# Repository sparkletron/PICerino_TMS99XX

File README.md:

# PICerino TMS VDP

Test Board and Software Library for TI TMS992X and TMS9118 video display processors.

author: Jay Convertino  

date: 2022.04.23  

license: MIT (software/Hardware)

## Release Versions
### Current
  - v2.1.0 - Improved video circuit for the TMS9118.

### Past
  - v2.0.0 - Improved video circuit that actually works.
  - v1.0.0 - Improved video circuit and TMS9118 schematic added.
  - v0.5.0 - First version with old video circuit.
  - none
  
## Requirements
### Hardware
  - KiCad
  
### Software
  - xc8 compiler
  
## Information

### Directory Listing:

  - docs - Data documents for various ICs.
  - schematic - KiCad schematic
    - TMS9118 - Contains a schematic for a TMS9118 board with video circuit (v2).
    - TMS992X - Contains a schematic for a TMS992X board with video circuit (v2).
  - src - Any source code for the project.
    - lib_picTMS99XX folder contains a library with test program for picerino. See readme.md in this directory for details.

### Usage
  This is made to be used with the picerino development board. This uses the standard DRAM since there are plenty of them around from various venders. The idea is the test program with put the card through its paces. This is done by putting the VDP into all modes and testing all of its functions. Currently this is incomplete. GFX II, various sprite sizes and edge cases need testing. The other idea with this was to create a simple video circuit for YrYbY output to go to an upscaler and then to HDMI. The retrotink 2x works well with the output of this unit.

### Build
  Through hole components were selected for everything, except for the video circuit of the TMS9118. This something I had on hand. Production uses a double sided board.

### Video Output
  This video circuit is based on a few ideas. Mostly TMS-RGB for the use of the LM1881. All other design choices are from application datasheets and just trial and error. Main issue with TMS-RGB being used whole sale is it has all surface mount components and it isn't universal for TMS9918. The goal of this project was to output component or composite to the retro tink x2. TI's application data sheet is keying out the Yr/Yb color bursts with a decoulping cap passing the signal to a 4066 that just went to ground during sync. This in theory should work fine, but in practice you'll still see a bit of the burst. TMS-RGB used a sample and hold method, which worked great to the converter chip. Taking the TMS RGB and just using a quad switch to sample the Yb signal, then pass it to the other inputs that then use that sample when needed (see lm1881 connections). This method of using a quad switch eliminates the too much blue issue. It also results in a circuit that is only 3 ic's. A MAX394, ADG813, and LM1881. The opamp is setup to rebalance the colors per the TMS RGB Y+Yr+Yb findings. Again big thanks to them for spending the time to document how and what they did. Saved me a lot of work on this project.

### Issues
  N/A

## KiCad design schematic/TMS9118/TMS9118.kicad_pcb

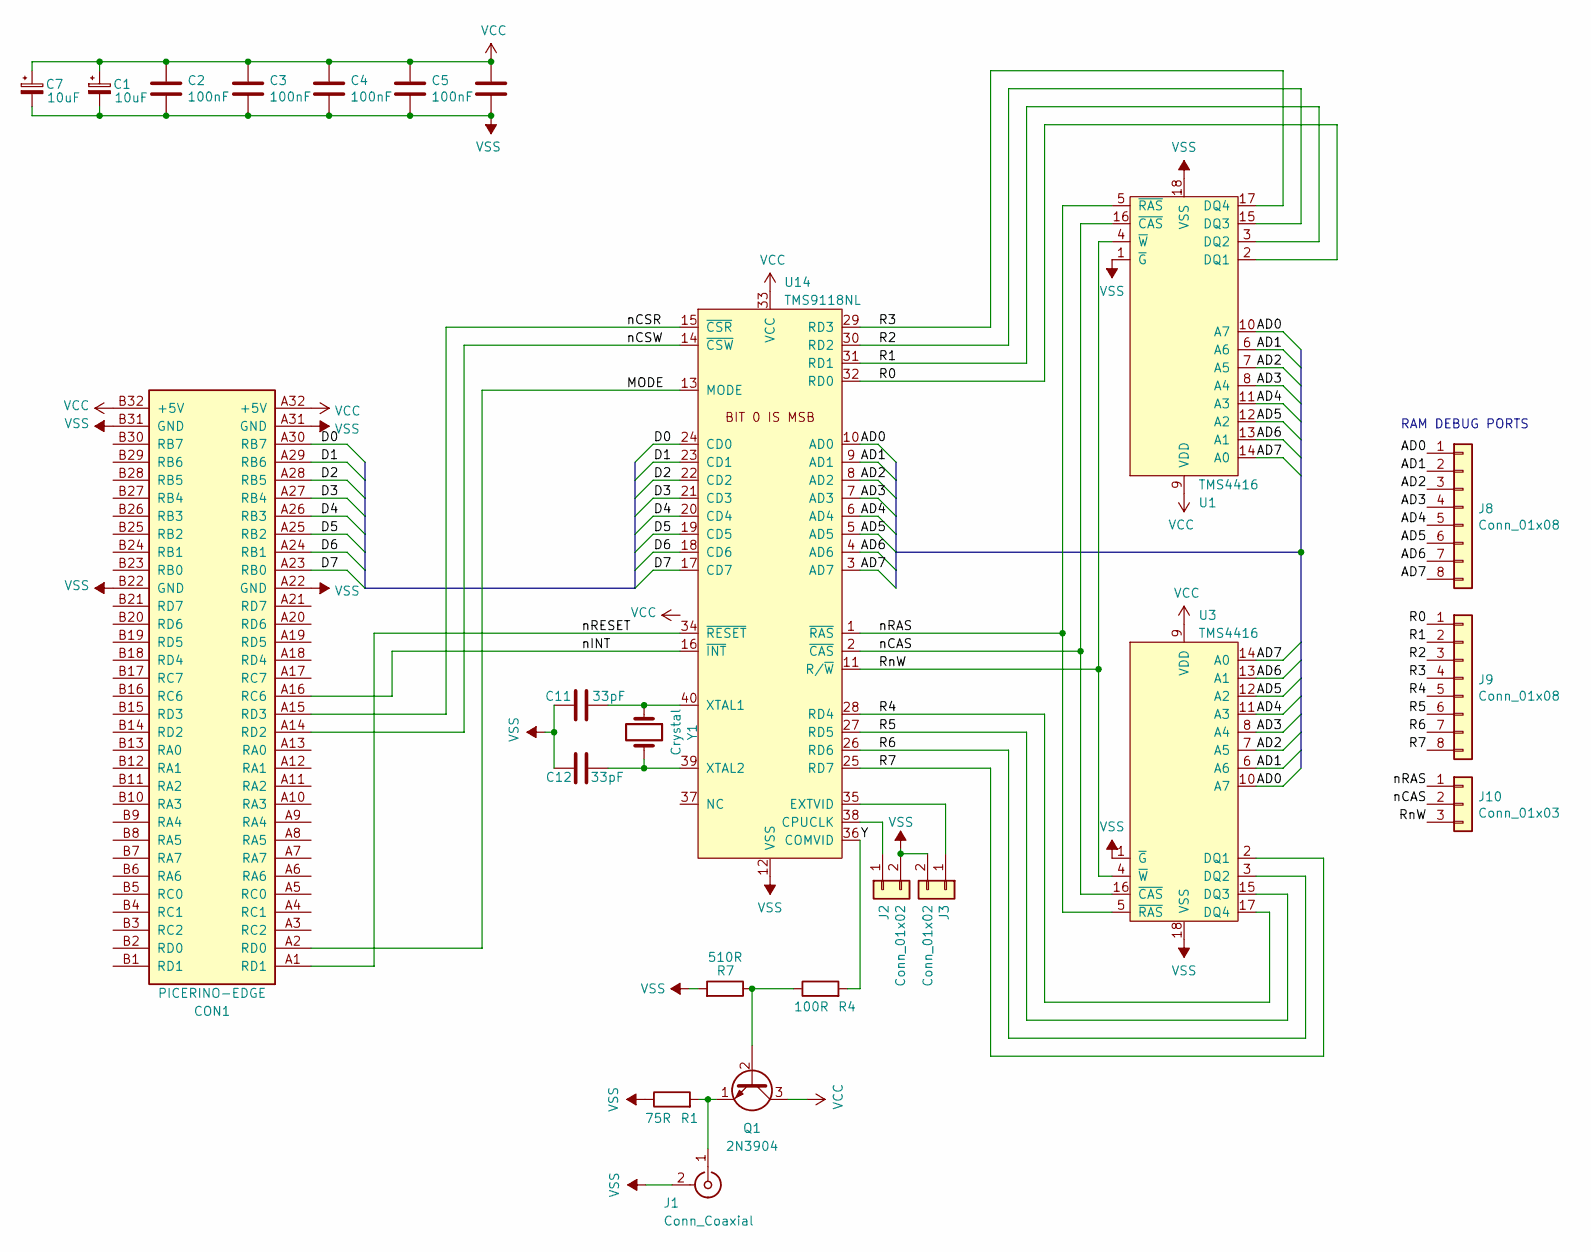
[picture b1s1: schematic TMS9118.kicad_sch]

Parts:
C1, C7: 10uF; CP_Radial_D5.0mm_P2.50mm
C2, C3, C4, C5, C6: 100nF; C_Disc_D4.7mm_W2.5mm_P5.00mm
C11, C12: 33pF; C_Disc_D3.0mm_W1.6mm_P2.50mm
CON1: PICERINO-EDGE
J1: Conn_Coaxial; RCJ041
J2, J3: Conn_01x02; PinHeader_1x02_P2.54mm_Vertical
J8, J9: Conn_01x08; SIP-8_19x3mm_P2.54mm
J10: Conn_01x03; PinHeader_1x03_P2.54mm_Vertical
Q1: 2N3904; TO-92_Wide
R1: 75R; R_Axial_DIN0207_L6.3mm_D2.5mm_P7.62mm_Horizontal
R4: 100R; R_Axial_DIN0207_L6.3mm_D2.5mm_P7.62mm_Horizontal
R7: 510R; R_Axial_DIN0207_L6.3mm_D2.5mm_P7.62mm_Horizontal
U1, U3: TMS4416; DIP-18_W7.62mm_LongPads
U14: TMS9118NL; DIP-40_W15.24mm_LongPads
Y1: Crystal; Crystal_HC49-4H_Vertical

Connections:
/AD0: J8.1, U1.10 (A7), U3.10 (A7), U14.10 (AD0)
/AD1: J8.2, U1.6 (A6), U3.6 (A6), U14.9 (AD1)
/AD2: J8.3, U1.7 (A5), U3.7 (A5), U14.8 (AD2)
/AD3: J8.4, U1.8 (A4), U3.8 (A4), U14.7 (AD3)
/AD4: J8.5, U1.11 (A3), U3.11 (A3), U14.6 (AD4)
/AD5: J8.6, U1.12 (A2), U3.12 (A2), U14.5 (AD5)
/AD6: J8.7, U1.13 (A1), U3.13 (A1), U14.4 (AD6)
/AD7: J8.8, U1.14 (A0), U3.14 (A0), U14.3 (AD7)
/D0: CON1.A30 (RB7), U14.24 (CD0)
/D1: CON1.A29 (RB6), U14.23 (CD1)
/D2: CON1.A28 (RB5), U14.22 (CD2)
/D3: CON1.A27 (RB4), U14.21 (CD3)
/D4: CON1.A26 (RB3), U14.20 (CD4)
/D5: CON1.A25 (RB2), U14.19 (CD5)
/D6: CON1.A24 (RB1), U14.18 (CD6)
/D7: CON1.A23 (RB0), U14.17 (CD7)
/MODE: CON1.A2 (RD0), U14.13 (MODE)
/R0: J9.1, U1.2 (DQ1), U14.32 (RD0)
/R1: J9.2, U1.3 (DQ2), U14.31 (RD1)
/R2: J9.3, U1.15 (DQ3), U14.30 (RD2)
/R3: J9.4, U1.17 (DQ4), U14.29 (RD3)
/R4: J9.5, U3.17 (DQ4), U14.28 (RD4)
/R5: J9.6, U3.15 (DQ3), U14.27 (RD5)
/R6: J9.7, U3.3 (DQ2), U14.26 (RD6)
/R7: J9.8, U3.2 (DQ1), U14.25 (RD7)
/RnW: J10.3, U1.4 (~W), U3.4 (~W), U14.11 (R/~W)
/Y: R4.2, U14.36 (COMVID)
/nCAS: J10.2, U1.16 (~CAS), U3.16 (~CAS), U14.2 (~CAS)
/nCSR: CON1.A15 (RD3), U14.15 (~CSR)
/nCSW: CON1.A14 (RD2), U14.14 (~CSW)
/nINT: CON1.A16 (RC6), U14.16 (~INT)
/nRAS: J10.1, U1.5 (~RAS), U3.5 (~RAS), U14.1 (~RAS)
/nRESET: CON1.A1 (RD1), U14.34 (~RESET)
unnamed: J1.1 (In), Q1.1 (E), R1.2
unnamed: J2.1, U14.38 (CPUCLK)
unnamed: J3.1, U14.35 (EXTVID)
unnamed: Q1.2 (B), R4.1, R7.1
unnamed: C11.2, U14.40 (XTAL1), Y1.1
unnamed: C12.1, U14.39 (XTAL2), Y1.2
VCC: C1.1, C2.1, C3.1, C4.1, C5.1, C6.1, C7.1, CON1.A32 (+5V), CON1.B32 (+5V), Q1.3 (C), U1.9 (VDD), U3.9 (VDD), U14.33 (VCC)
VSS: C1.2, C2.2, C3.2, C4.2, C5.2, C6.2, C7.2, C11.1, C12.2, CON1.A22 (GND), CON1.A31 (GND), CON1.B22 (GND), CON1.B31 (GND), J1.2 (Ext), J2.2, J3.2, R1.1, R7.2, U1.1 (~G), U1.18 (VSS), U3.1 (~G), U3.18 (VSS), U14.12 (VSS)

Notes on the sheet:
RAM DEBUG PORTS

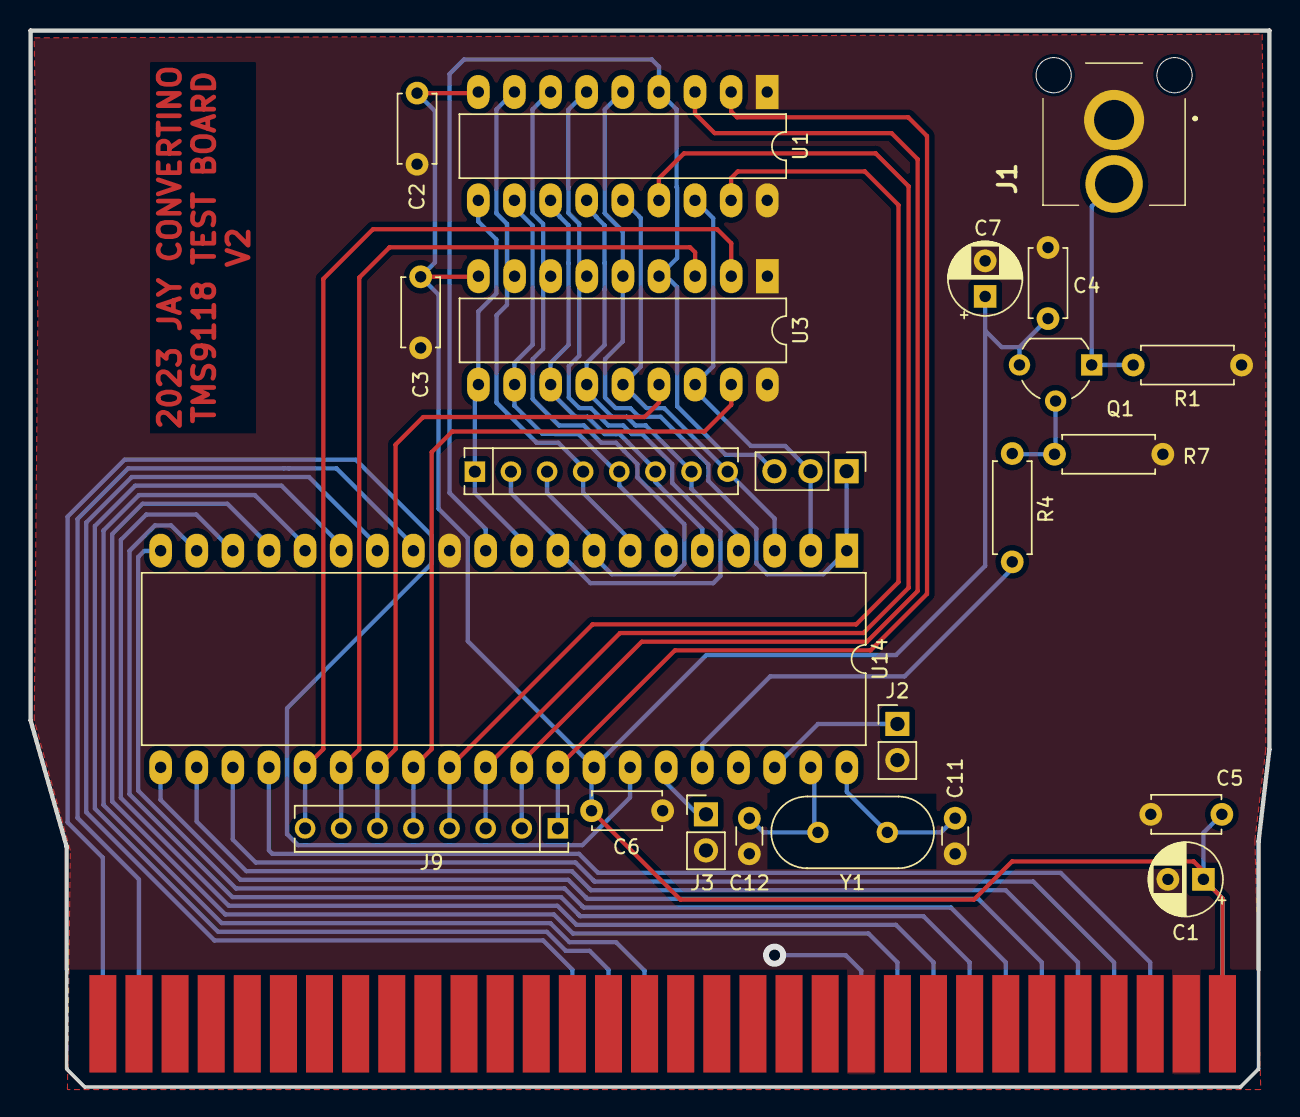
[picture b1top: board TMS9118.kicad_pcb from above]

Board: 2 copper layers, 87.1 x 74.3 mm, 24 parts (0 on the bottom side), 41 nets.

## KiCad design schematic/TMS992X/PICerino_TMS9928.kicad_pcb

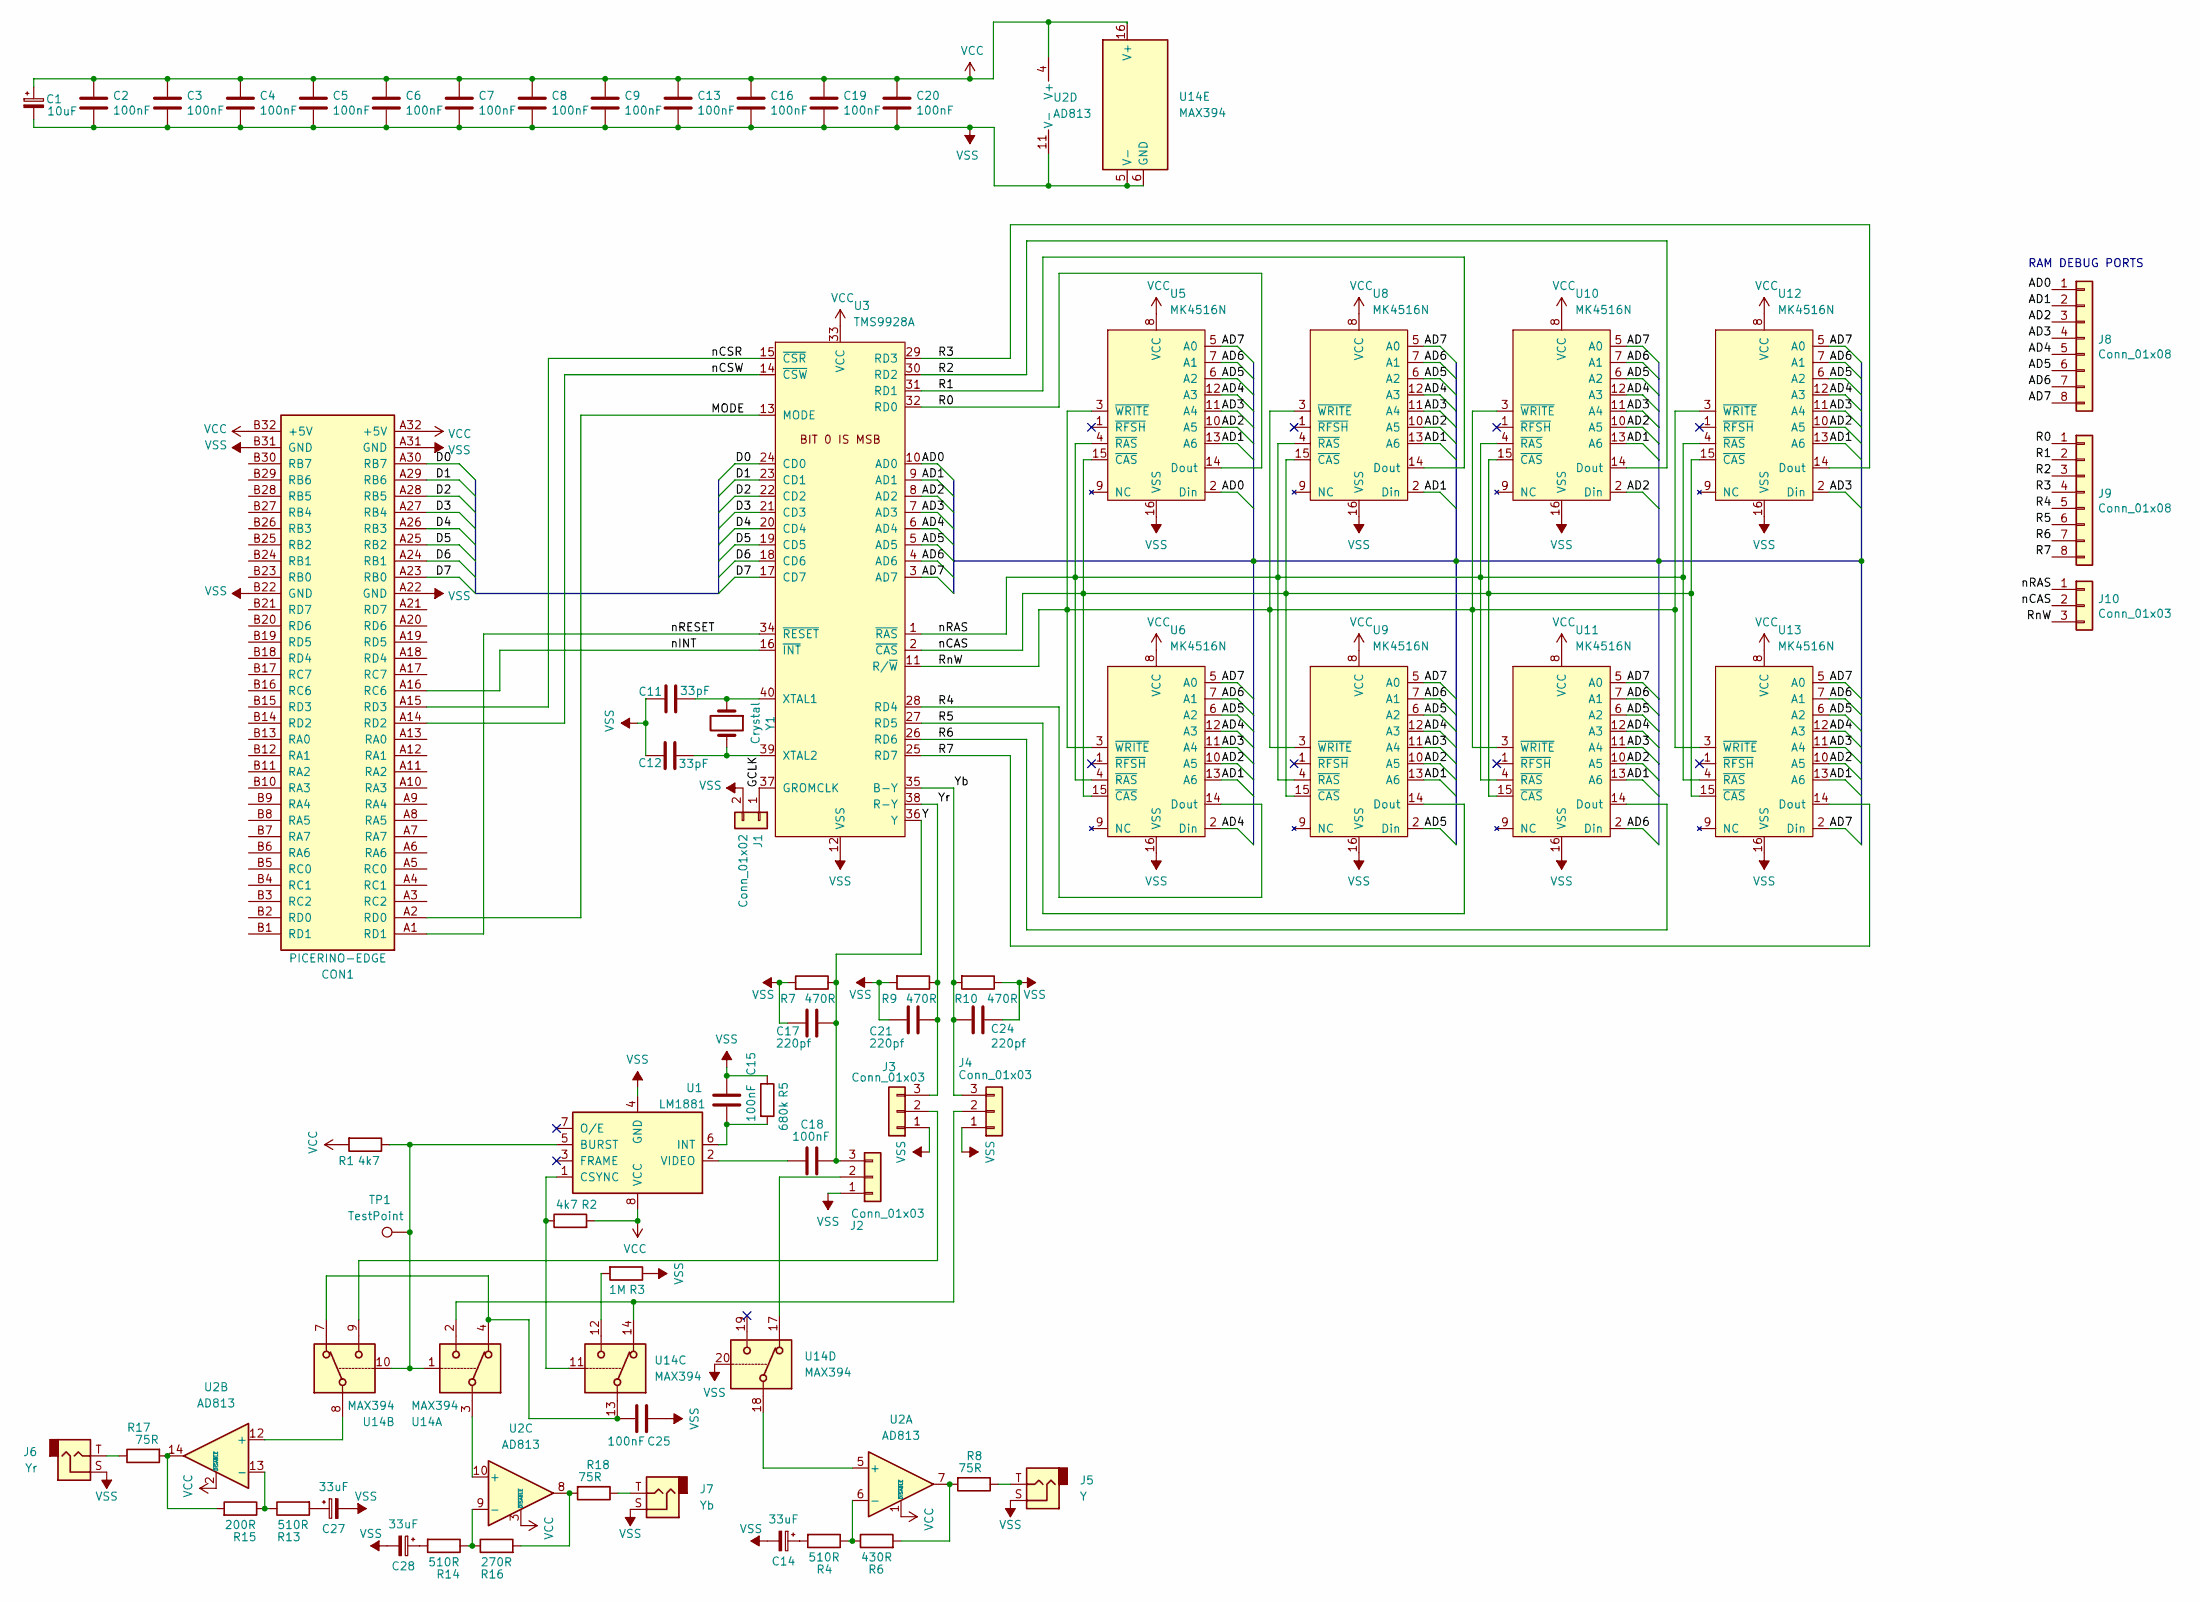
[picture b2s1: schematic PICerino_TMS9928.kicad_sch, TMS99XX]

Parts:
C1: 10uF; CP_Radial_D5.0mm_P2.50mm
C2, C3, C4, C5, C6, C7, C8, C9, C13, C15, C16, C18, C19, C20, C25: 100nF; C_Disc_D4.7mm_W2.5mm_P5.00mm
C11, C12: 33pF; C_Disc_D3.0mm_W1.6mm_P2.50mm
C14, C27, C28: 33uF; CP_Radial_D5.0mm_P2.50mm
C17, C21, C24: 220pf; C_Disc_D4.7mm_W2.5mm_P5.00mm
CON1: PICERINO-EDGE
J1: Conn_01x02; PinHeader_1x02_P2.54mm_Vertical
J2, J3, J4, J10: Conn_01x03; PinHeader_1x03_P2.54mm_Vertical
J5: Y; RCJ041_TS
J6: Yr; RCJ041_TS
J7: Yb; RCJ041_TS
J8, J9: Conn_01x08; SIP-8_19x3mm_P2.54mm
R1, R2: 4k7; R_Axial_DIN0207_L6.3mm_D2.5mm_P7.62mm_Horizontal
R3: 1M; R_Axial_DIN0207_L6.3mm_D2.5mm_P7.62mm_Horizontal
R4, R13, R14: 510R; R_Axial_DIN0207_L6.3mm_D2.5mm_P7.62mm_Horizontal
R5: 680k; R_Axial_DIN0207_L6.3mm_D2.5mm_P7.62mm_Horizontal
R6: 430R; R_Axial_DIN0207_L6.3mm_D2.5mm_P7.62mm_Horizontal
R7, R9, R10: 470R; R_Axial_DIN0207_L6.3mm_D2.5mm_P7.62mm_Horizontal
R8, R17, R18: 75R; R_Axial_DIN0207_L6.3mm_D2.5mm_P7.62mm_Horizontal
R15: 200R; R_Axial_DIN0207_L6.3mm_D2.5mm_P7.62mm_Horizontal
R16: 270R; R_Axial_DIN0207_L6.3mm_D2.5mm_P7.62mm_Horizontal
TP1: TestPoint; PinHeader_1x01_P2.54mm_Vertical
U1: LM1881; DIP-8_W7.62mm_LongPads
U2: AD813; DIP-14_W7.62mm_LongPads
U3: TMS9928A; DIP-40_W15.24mm_LongPads
U5, U6, U8, U9, U10, U11, U12, U13: MK4516N; DIP-16_W7.62mm_LongPads
U14: MAX394; DIP-20_W7.62mm_LongPads
Y1: Crystal; Crystal_HC49-4H_Vertical

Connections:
/AD0: J8.1, U3.10 (AD0), U5.2 (Din)
/AD1: J8.2, U3.9 (AD1), U5.13 (A6), U6.13 (A6), U8.2 (Din), U8.13 (A6), U9.13 (A6), U10.13 (A6), U11.13 (A6), U12.13 (A6), U13.13 (A6)
/AD2: J8.3, U3.8 (AD2), U5.10 (A5), U6.10 (A5), U8.10 (A5), U9.10 (A5), U10.2 (Din), U10.10 (A5), U11.10 (A5), U12.10 (A5), U13.10 (A5)
/AD3: J8.4, U3.7 (AD3), U5.11 (A4), U6.11 (A4), U8.11 (A4), U9.11 (A4), U10.11 (A4), U11.11 (A4), U12.2 (Din), U12.11 (A4), U13.11 (A4)
/AD4: J8.5, U3.6 (AD4), U5.12 (A3), U6.2 (Din), U6.12 (A3), U8.12 (A3), U9.12 (A3), U10.12 (A3), U11.12 (A3), U12.12 (A3), U13.12 (A3)
/AD5: J8.6, U3.5 (AD5), U5.6 (A2), U6.6 (A2), U8.6 (A2), U9.2 (Din), U9.6 (A2), U10.6 (A2), U11.6 (A2), U12.6 (A2), U13.6 (A2)
/AD6: J8.7, U3.4 (AD6), U5.7 (A1), U6.7 (A1), U8.7 (A1), U9.7 (A1), U10.7 (A1), U11.2 (Din), U11.7 (A1), U12.7 (A1), U13.7 (A1)
/AD7: J8.8, U3.3 (AD7), U5.5 (A0), U6.5 (A0), U8.5 (A0), U9.5 (A0), U10.5 (A0), U11.5 (A0), U12.5 (A0), U13.2 (Din), U13.5 (A0)
/D0: CON1.A30 (RB7), U3.24 (CD0)
/D1: CON1.A29 (RB6), U3.23 (CD1)
/D2: CON1.A28 (RB5), U3.22 (CD2)
/D3: CON1.A27 (RB4), U3.21 (CD3)
/D4: CON1.A26 (RB3), U3.20 (CD4)
/D5: CON1.A25 (RB2), U3.19 (CD5)
/D6: CON1.A24 (RB1), U3.18 (CD6)
/D7: CON1.A23 (RB0), U3.17 (CD7)
/GCLK: J1.1, U3.37 (GROMCLK)
/MODE: CON1.A2 (RD0), U3.13 (MODE)
/R0: J9.1, U3.32 (RD0), U5.14 (Dout)
/R1: J9.2, U3.31 (RD1), U8.14 (Dout)
/R2: J9.3, U3.30 (RD2), U10.14 (Dout)
/R3: J9.4, U3.29 (RD3), U12.14 (Dout)
/R4: J9.5, U3.28 (RD4), U6.14 (Dout)
/R5: J9.6, U3.27 (RD5), U9.14 (Dout)
/R6: J9.7, U3.26 (RD6), U11.14 (Dout)
/R7: J9.8, U3.25 (RD7), U13.14 (Dout)
/RnW: J10.3, U3.11 (R/~W), U5.3 (~WRITE), U6.3 (~WRITE), U8.3 (~WRITE), U9.3 (~WRITE), U10.3 (~WRITE), U11.3 (~WRITE), U12.3 (~WRITE), U13.3 (~WRITE)
/Y: C17.1, C18.1, J2.3, R7.1, U3.36 (Y)
/Yb: C24.2, J4.3, R10.2, U3.35 (B-Y)
/Yr: C21.1, J3.3, R9.1, U3.38 (R-Y)
/nCAS: J10.2, U3.2 (~CAS), U5.15 (~CAS), U6.15 (~CAS), U8.15 (~CAS), U9.15 (~CAS), U10.15 (~CAS), U11.15 (~CAS), U12.15 (~CAS), U13.15 (~CAS)
/nCSR: CON1.A15 (RD3), U3.15 (~CSR)
/nCSW: CON1.A14 (RD2), U3.14 (~CSW)
/nINT: CON1.A16 (RC6), U3.16 (~INT)
/nRAS: J10.1, U3.1 (~RAS), U5.4 (~RAS), U6.4 (~RAS), U8.4 (~RAS), U9.4 (~RAS), U10.4 (~RAS), U11.4 (~RAS), U12.4 (~RAS), U13.4 (~RAS)
/nRESET: CON1.A1 (RD1), U3.34 (~RESET)
unnamed: C14.1, R4.2
unnamed: C25.2, U14.4, U14.7, U14.13
unnamed: C27.1, R13.2
unnamed: C28.1, R14.2
unnamed: J2.2, U14.17
unnamed: J3.2, U14.9
unnamed: J4.2, U14.2, U14.14
unnamed: J5.T, R8.1
unnamed: J6.T, R17.1
unnamed: J7.T, R18.1
unnamed: R3.2, U14.12
unnamed: R6.2, R8.2, U2.7
unnamed: R15.2, R17.2, U2.14
unnamed: R16.2, R18.2, U2.8
unnamed: R1.1, TP1.1, U1.5 (BURST), U14.1, U14.10
unnamed: R2.1, U1.1 (CSYNC), U14.11
unnamed: C15.1, R5.2, U1.6 (INT)
unnamed: C18.2, U1.2 (VIDEO)
unnamed: U2.5 (+), U14.18
unnamed: R4.1, R6.1, U2.6 (-)
unnamed: U2.12 (+), U14.8
unnamed: R13.1, R15.1, U2.13 (-)
unnamed: U2.10 (+), U14.3
unnamed: R14.1, R16.1, U2.9 (-)
unnamed: C11.2, U3.40 (XTAL1), Y1.1
unnamed: C12.1, U3.39 (XTAL2), Y1.2
VCC: C1.1, C2.1, C3.1, C4.1, C5.1, C6.1, C7.1, C8.1, C9.1, C13.1, C16.1, C19.1, C20.1, CON1.A32 (+5V), CON1.B32 (+5V), R1.2, R2.2, U1.8 (VCC), U2.1 (~DISABLE), U2.2 (~DISABLE), U2.3 (~DISABLE), U2.4 (V+), U3.33 (VCC), U5.8 (VCC), U6.8 (VCC), U8.8 (VCC), U9.8 (VCC), U10.8 (VCC), U11.8 (VCC), U12.8 (VCC), U13.8 (VCC), U14.16 (V+)
VSS: C1.2, C2.2, C3.2, C4.2, C5.2, C6.2, C7.2, C8.2, C9.2, C11.1, C12.2, C13.2, C14.2, C15.2, C16.2, C17.2, C19.2, C20.2, C21.2, C24.1, C25.1, C27.2, C28.2, CON1.A22 (GND), CON1.A31 (GND), CON1.B22 (GND), CON1.B31 (GND), J1.2, J2.1, J3.1, J4.1, J5.S, J6.S, J7.S, R3.1, R5.1, R7.2, R9.2, R10.1, U1.4 (GND), U2.11 (V-), U3.12 (VSS), U5.16 (VSS), U6.16 (VSS), U8.16 (VSS), U9.16 (VSS), U10.16 (VSS), U11.16 (VSS), U12.16 (VSS), U13.16 (VSS), U14.5 (V-), U14.6 (GND), U14.20

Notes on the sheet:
RAM DEBUG PORTS

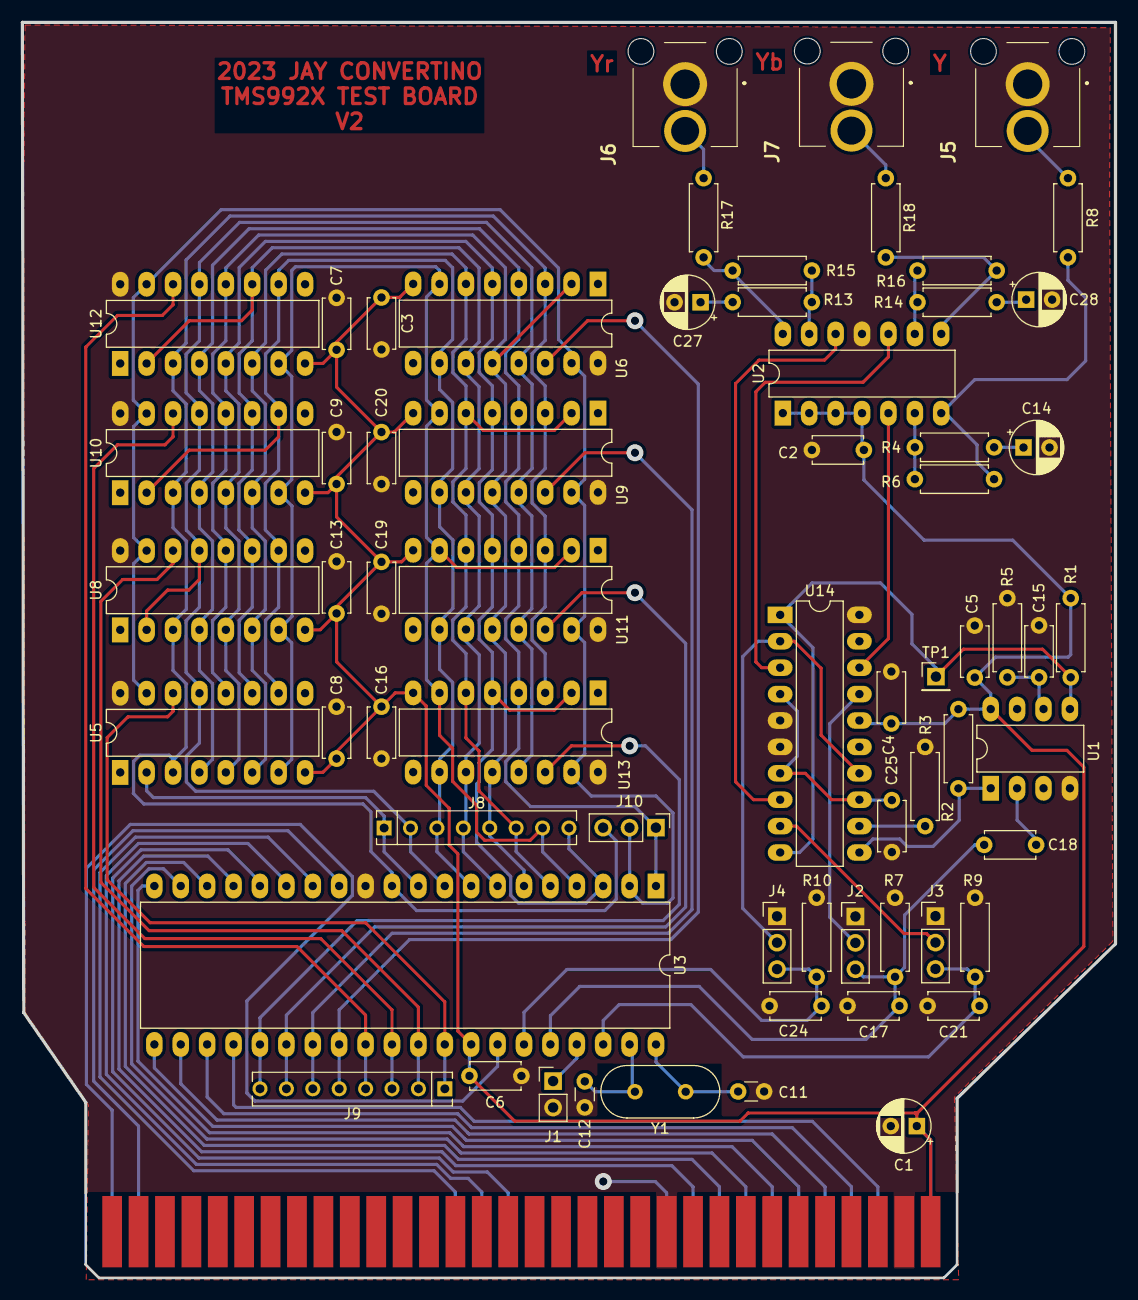
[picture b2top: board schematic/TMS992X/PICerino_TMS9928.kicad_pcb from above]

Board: 2 copper layers, 105.2 x 120.8 mm, 65 parts (0 on the bottom side), 64 nets.

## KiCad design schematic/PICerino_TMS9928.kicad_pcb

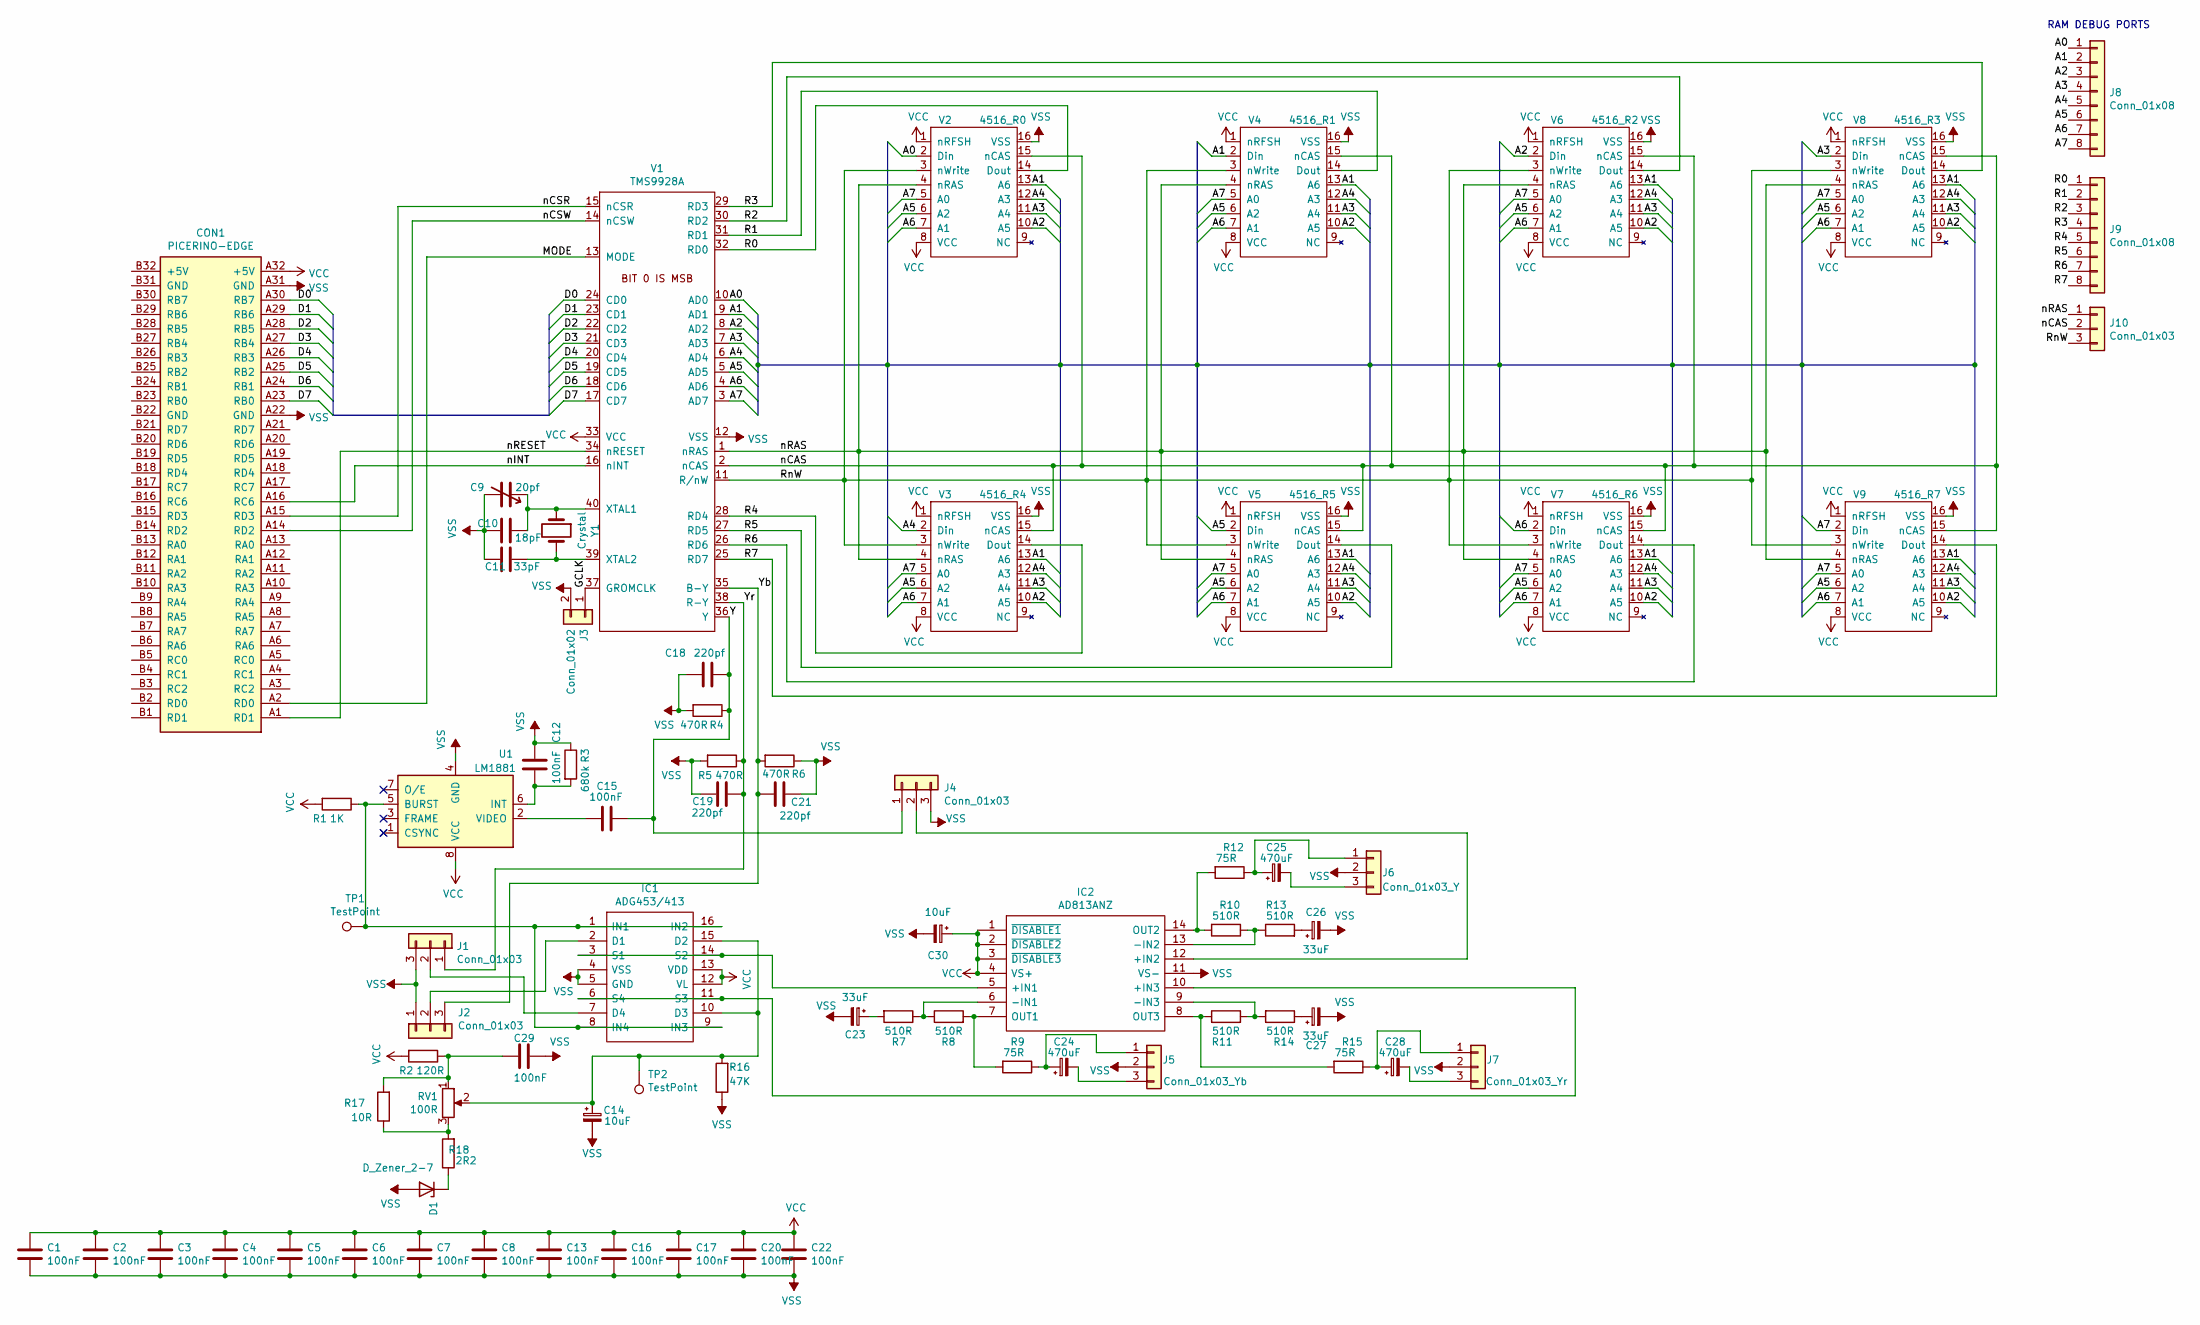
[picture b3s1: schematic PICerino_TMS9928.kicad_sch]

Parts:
C1, C2, C3, C4, C5, C6, C7, C8, C12, C13, C15, C16, C17, C20, C22, C29: 100nF; C_Disc_D4.7mm_W2.5mm_P5.00mm
C9: 20pf; C_Rect_L10.0mm_W5.0mm_P5.00mm_P7.50mm
C10: 18pF; C_Disc_D3.0mm_W1.6mm_P2.50mm
C11: 33pF; C_Disc_D3.0mm_W1.6mm_P2.50mm
C14, C30: 10uF; CP_Radial_D5.0mm_P2.50mm
C18, C19, C21: 220pf; C_Disc_D4.7mm_W2.5mm_P5.00mm
C23, C26, C27: 33uF; CP_Radial_D5.0mm_P2.50mm
C24, C25, C28: 470uF; CP_Radial_D8.0mm_P5.00mm
CON1: PICERINO-EDGE
D1: D_Zener_2-7; D_DO-34_SOD68_P7.62mm_Horizontal
IC1: ADG453/413; DIP-16_W7.62mm_LongPads; Manufacturer_Part_Number ADG453BNZ
IC2: AD813ANZ; DIP-14_W7.62mm_LongPads; Manufacturer_Part_Number AD813ANZ
J1, J2, J4, J10: Conn_01x03; PinHeader_1x03_P2.54mm_Vertical
J3: Conn_01x02; PinHeader_1x02_P2.54mm_Vertical
J5: Conn_01x03_Yb; PinHeader_1x03_P2.54mm_Vertical
J6: Conn_01x03_Y; PinHeader_1x03_P2.54mm_Vertical
J7: Conn_01x03_Yr; PinHeader_1x03_P2.54mm_Vertical
J8, J9: Conn_01x08; SIP-8_19x3mm_P2.54mm
R1: 1K; R_Axial_DIN0207_L6.3mm_D2.5mm_P7.62mm_Horizontal
R2: 120R; R_Axial_DIN0207_L6.3mm_D2.5mm_P7.62mm_Horizontal
R3: 680k; R_Axial_DIN0207_L6.3mm_D2.5mm_P7.62mm_Horizontal
R4, R5, R6: 470R; R_Axial_DIN0207_L6.3mm_D2.5mm_P7.62mm_Horizontal
R7, R8, R10, R11, R13, R14: 510R; R_Axial_DIN0207_L6.3mm_D2.5mm_P7.62mm_Horizontal
R9, R12, R15: 75R; R_Axial_DIN0207_L6.3mm_D2.5mm_P7.62mm_Horizontal
R16: 47K; R_Axial_DIN0207_L6.3mm_D2.5mm_P7.62mm_Horizontal
R17: 10R; R_Axial_DIN0207_L6.3mm_D2.5mm_P7.62mm_Horizontal
R18: 2R2; R_Axial_DIN0207_L6.3mm_D2.5mm_P7.62mm_Horizontal
RV1: 100R; Potentiometer_Piher_PT-6-V_Vertical
TP1, TP2: TestPoint; PinHeader_1x01_P2.54mm_Vertical
U1: LM1881; DIP-8_W7.62mm_LongPads
V1: TMS9928A; DIP-40_W15.24mm_LongPads
V2: 4516_R0; DIP-16_W7.62mm_LongPads
V3: 4516_R4; DIP-16_W7.62mm_LongPads
V4: 4516_R1; DIP-16_W7.62mm_LongPads
V5: 4516_R5; DIP-16_W7.62mm_LongPads
V6: 4516_R2; DIP-16_W7.62mm_LongPads
V7: 4516_R6; DIP-16_W7.62mm_LongPads
V8: 4516_R3; DIP-16_W7.62mm_LongPads
V9: 4516_R7; DIP-16_W7.62mm_LongPads
Y1: Crystal; Crystal_HC49-4H_Vertical

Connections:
/A0: J8.1, V1.10 (AD0), V2.2 (Din)
/A1: J8.2, V1.9 (AD1), V2.13 (A6), V3.13 (A6), V4.2 (Din), V4.13 (A6), V5.13 (A6), V6.13 (A6), V7.13 (A6), V8.13 (A6), V9.13 (A6)
/A2: J8.3, V1.8 (AD2), V2.10 (A5), V3.10 (A5), V4.10 (A5), V5.10 (A5), V6.2 (Din), V6.10 (A5), V7.10 (A5), V8.10 (A5), V9.10 (A5)
/A3: J8.4, V1.7 (AD3), V2.11 (A4), V3.11 (A4), V4.11 (A4), V5.11 (A4), V6.11 (A4), V7.11 (A4), V8.2 (Din), V8.11 (A4), V9.11 (A4)
/A4: J8.5, V1.6 (AD4), V2.12 (A3), V3.2 (Din), V3.12 (A3), V4.12 (A3), V5.12 (A3), V6.12 (A3), V7.12 (A3), V8.12 (A3), V9.12 (A3)
/A5: J8.6, V1.5 (AD5), V2.6 (A2), V3.6 (A2), V4.6 (A2), V5.2 (Din), V5.6 (A2), V6.6 (A2), V7.6 (A2), V8.6 (A2), V9.6 (A2)
/A6: J8.7, V1.4 (AD6), V2.7 (A1), V3.7 (A1), V4.7 (A1), V5.7 (A1), V6.7 (A1), V7.2 (Din), V7.7 (A1), V8.7 (A1), V9.7 (A1)
/A7: J8.8, V1.3 (AD7), V2.5 (A0), V3.5 (A0), V4.5 (A0), V5.5 (A0), V6.5 (A0), V7.5 (A0), V8.5 (A0), V9.2 (Din), V9.5 (A0)
/D0: CON1.A30 (RB7), V1.24 (CD0)
/D1: CON1.A29 (RB6), V1.23 (CD1)
/D2: CON1.A28 (RB5), V1.22 (CD2)
/D3: CON1.A27 (RB4), V1.21 (CD3)
/D4: CON1.A26 (RB3), V1.20 (CD4)
/D5: CON1.A25 (RB2), V1.19 (CD5)
/D6: CON1.A24 (RB1), V1.18 (CD6)
/D7: CON1.A23 (RB0), V1.17 (CD7)
/GCLK: J3.1, V1.37 (GROMCLK)
/MODE: CON1.A2 (RD0), V1.13 (MODE)
/R0: J9.1, V1.32 (RD0), V2.14 (Dout)
/R1: J9.2, V1.31 (RD1), V4.14 (Dout)
/R2: J9.3, V1.30 (RD2), V6.14 (Dout)
/R3: J9.4, V1.29 (RD3), V8.14 (Dout)
/R4: J9.5, V1.28 (RD4), V3.14 (Dout)
/R5: J9.6, V1.27 (RD5), V5.14 (Dout)
/R6: J9.7, V1.26 (RD6), V7.14 (Dout)
/R7: J9.8, V1.25 (RD7), V9.14 (Dout)
/RnW: J10.3, V1.11 (R/nW), V2.3 (nWrite), V3.3 (nWrite), V4.3 (nWrite), V5.3 (nWrite), V6.3 (nWrite), V7.3 (nWrite), V8.3 (nWrite), V9.3 (nWrite)
/Y: C15.1, C18.1, J4.1, R4.1, V1.36 (Y)
/Yb: C21.2, J2.3, R6.2, V1.35 (B-Y)
/Yr: C19.1, J1.1, R5.1, V1.38 (R-Y)
/nCAS: J10.2, V1.2 (nCAS), V2.15 (nCAS), V3.15 (nCAS), V4.15 (nCAS), V5.15 (nCAS), V6.15 (nCAS), V7.15 (nCAS), V8.15 (nCAS), V9.15 (nCAS)
/nCSR: CON1.A15 (RD3), V1.15 (nCSR)
/nCSW: CON1.A14 (RD2), V1.14 (nCSW)
/nINT: CON1.A16 (RC6), V1.16 (nINT)
/nRAS: J10.1, V1.1 (nRAS), V2.4 (nRAS), V3.4 (nRAS), V4.4 (nRAS), V5.4 (nRAS), V6.4 (nRAS), V7.4 (nRAS), V8.4 (nRAS), V9.4 (nRAS)
/nRESET: CON1.A1 (RD1), V1.34 (nRESET)
unnamed: C9.1, C10.2, V1.40 (XTAL1), Y1.1
unnamed: C11.1, V1.39 (XTAL2), Y1.2
unnamed: C12.1, R3.2, U1.6 (INT)
unnamed: C14.1, IC1.10 (D3), IC1.15 (D2), R16.2, RV1.2, TP2.1
unnamed: C15.2, U1.2 (VIDEO)
unnamed: C23.1, R7.2
unnamed: C24.1, J5.1, R9.1
unnamed: C24.2, J5.3
unnamed: C25.1, J6.1, R12.1
unnamed: C25.2, J6.3
unnamed: C26.1, R13.2
unnamed: C27.1, R14.1
unnamed: C28.1, J7.1, R15.1
unnamed: C28.2, J7.3
unnamed: C29.2, R2.1, R17.2, RV1.1
unnamed: D1.1 (K), R18.1
unnamed: IC1.1 (IN1), IC1.8 (IN4), IC1.9 (IN3), IC1.16 (IN2), R1.1, TP1.1, U1.5 (BURST)
unnamed: IC1.2 (D1), J2.2
unnamed: IC1.7 (D4), J1.2
unnamed: IC1.6 (S4), IC1.11 (S3), IC2.10 (+IN3)
unnamed: IC1.3 (S1), IC1.14 (S2), IC2.5 (+IN1)
unnamed: IC2.6 (-IN1), R7.1, R8.1
unnamed: IC2.7 (OUT1), R8.2, R9.2
unnamed: IC2.8 (OUT3), R11.1, R15.2
unnamed: IC2.9 (-IN3), R11.2, R14.2
unnamed: IC2.12 (+IN2), J4.2
unnamed: IC2.13 (-IN2), R10.1, R13.1
unnamed: IC2.14 (OUT2), R10.2, R12.2
unnamed: R17.1, R18.2, RV1.3
VCC: C1.1, C2.1, C3.1, C4.1, C5.1, C6.1, C7.1, C8.1, C13.1, C16.1, C17.1, C20.1, C22.1, C30.1, CON1.A32 (+5V), IC1.12 (VL), IC1.13 (VDD), IC2.1 (~DISABLE1), IC2.2 (~DISABLE2), IC2.3 (~DISABLE3), IC2.4 (VS+), R1.2, R2.2, U1.8 (VCC), V1.33 (VCC), V2.1 (nRFSH), V2.8 (VCC), V3.1 (nRFSH), V3.8 (VCC), V4.1 (nRFSH), V4.8 (VCC), V5.1 (nRFSH), V5.8 (VCC), V6.1 (nRFSH), V6.8 (VCC), V7.1 (nRFSH), V7.8 (VCC), V8.1 (nRFSH), V8.8 (VCC), V9.1 (nRFSH), V9.8 (VCC)
VSS: C1.2, C2.2, C3.2, C4.2, C5.2, C6.2, C7.2, C8.2, C9.2, C10.1, C11.2, C12.2, C13.2, C14.2, C16.2, C17.2, C18.2, C19.2, C20.2, C21.1, C22.2, C23.2, C26.2, C27.2, C29.1, C30.2, CON1.A22 (GND), CON1.A31 (GND), D1.2 (A), IC1.4 (VSS), IC1.5 (GND), IC2.11 (VS-), J1.3, J2.1, J3.2, J4.3, J5.2, J6.2, J7.2, R3.1, R4.2, R5.2, R6.1, R16.1, U1.4 (GND), V1.12 (VSS), V2.16 (VSS), V3.16 (VSS), V4.16 (VSS), V5.16 (VSS), V6.16 (VSS), V7.16 (VSS), V8.16 (VSS), V9.16 (VSS)

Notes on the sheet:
RAM DEBUG PORTS

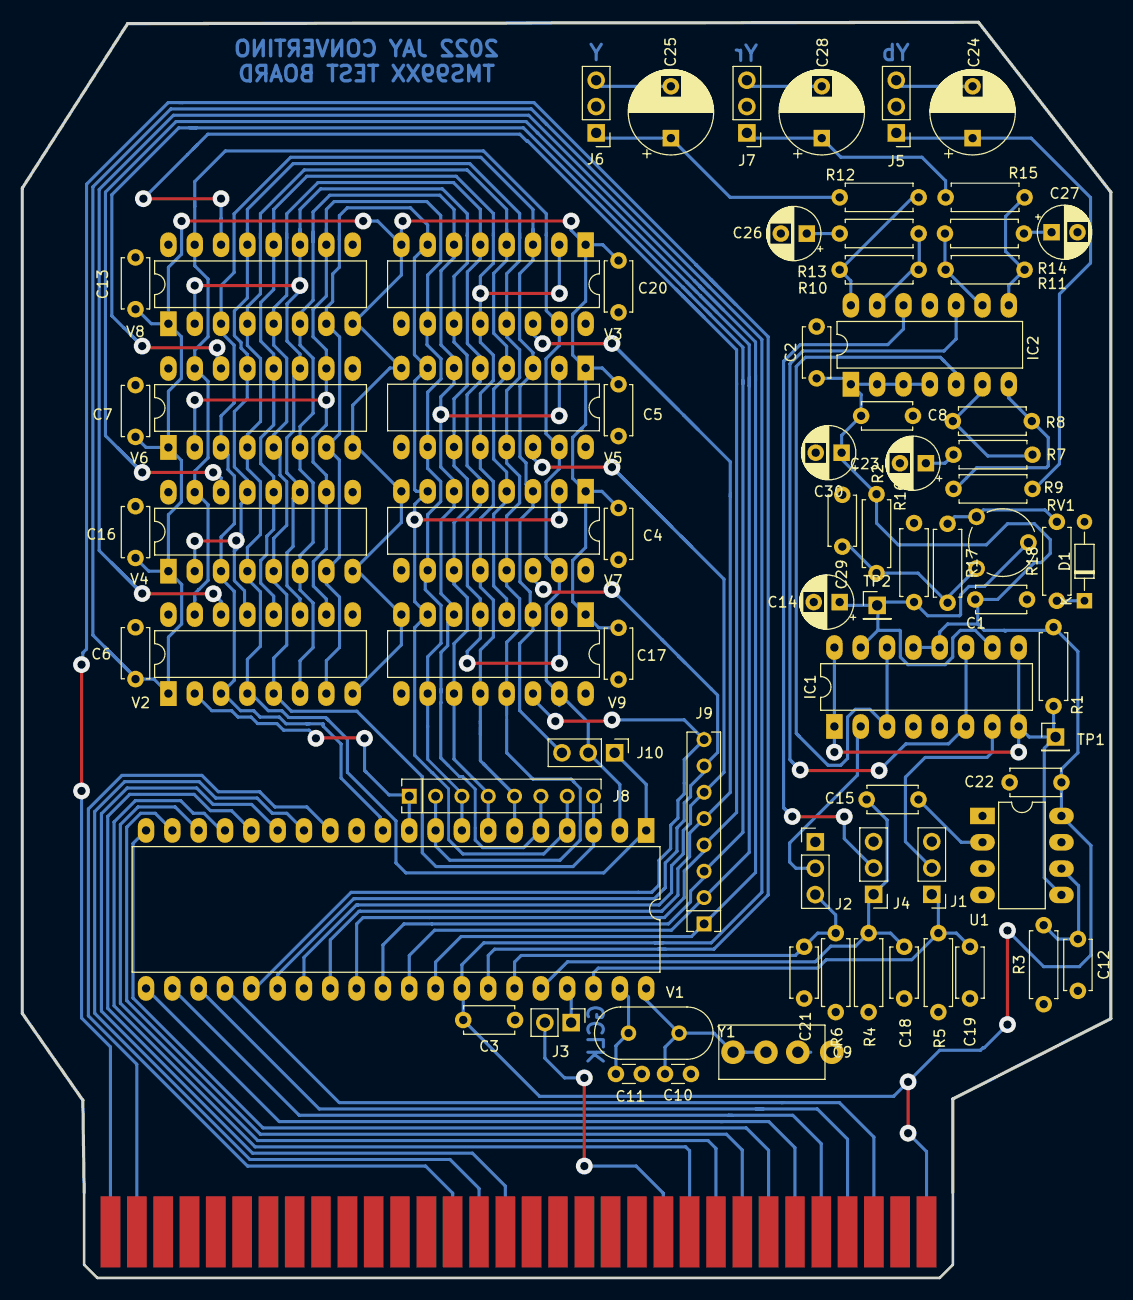
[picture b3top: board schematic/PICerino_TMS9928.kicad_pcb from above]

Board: 2 copper layers, 105.0 x 121.1 mm, 76 parts (0 on the bottom side), 67 nets.

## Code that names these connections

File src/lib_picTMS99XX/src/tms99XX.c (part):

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/*** write VDP vram ***/
inline int writeVDPvram(struct s_tms99XX * const p_tms99XX, uint8_t const * const p_data, int size, int modLen);
/*** set write or read VDP vram address ***/
inline void writeVDPvramAddr(struct s_tms99XX * const p_tms99XX, uint16_t address, int rnw);
/*** write VDP registers ***/
inline void writeVDPregister(struct s_tms99XX * const p_tms99XX, uint8_t regNum, uint8_t data);
/*** graphics mode ***/
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/** INITIALIZE AND FREE MY STRUCTS **/

/*** Initialize TMS99XX ports for correct I/O and set pin numbers ***/
void initTMS99XXport(struct s_tms99XX * const p_tms99XX, volatile unsigned char *p_dataTRIS, volatile unsigned char *p_ctrlTRIS, volatile unsigned char *p_intTRIS, uint8_t nCSR, uint8_t nCSW, uint8_t mode, uint8_t nreset, uint8_t nINT)
{
  /**** NULL Check ****/
  if(!p_tms99XX) return;
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}

/*** set write or read VDP vram address ***/
inline void writeVDPvramAddr(struct s_tms99XX * const p_tms99XX, uint16_t address, int rnw)
{
  /**** NULL Check ****/
  if(!p_tms99XX) return;
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

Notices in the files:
src/lib_picTMS99XX/src/tms99XX.c:
Copyright 2022 Johnathan Convertino
schematic/TMS9118/TMS9118.kicad_sch:
MIT License
